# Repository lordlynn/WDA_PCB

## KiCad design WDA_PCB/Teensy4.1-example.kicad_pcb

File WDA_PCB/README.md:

# Description
Basic PCB design to go along with the code developed for Wireless Data Acquisition.

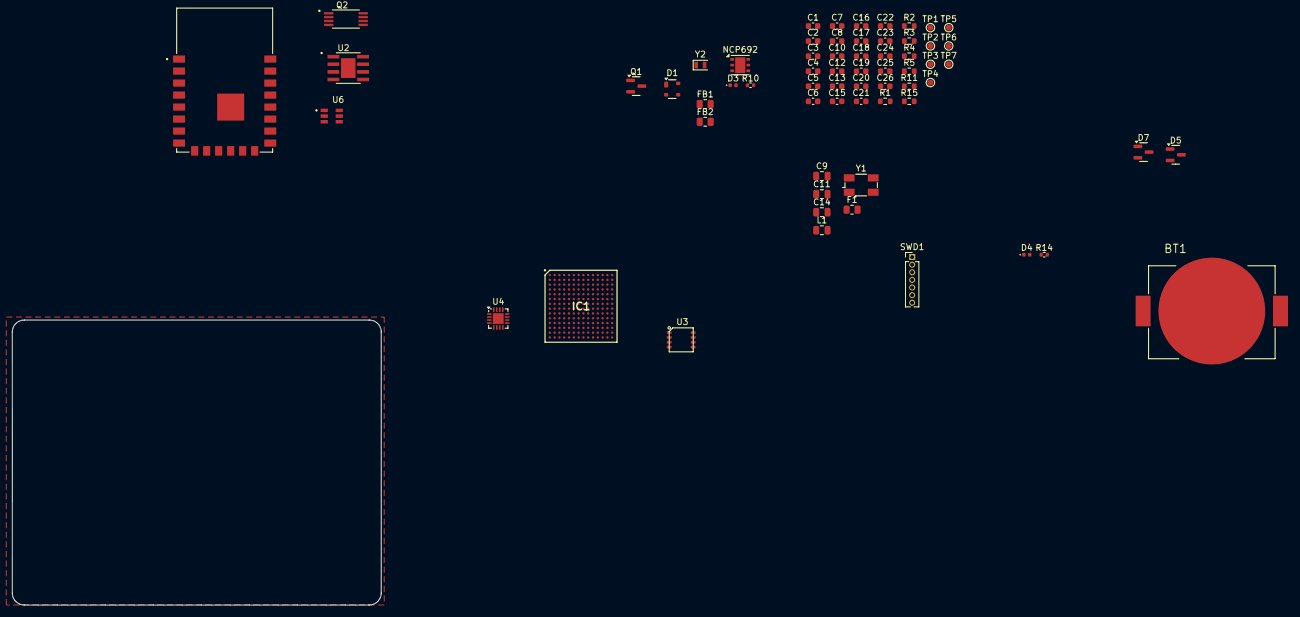
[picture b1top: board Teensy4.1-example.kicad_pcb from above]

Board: 4 copper layers, 61.5 x 47.5 mm, 64 parts (0 on the bottom side), 49 nets, no tracks yet.

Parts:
BT1: BAT-HLD-001; BAT_BAT-HLD-001
C1, C2, C4, C8, C10, C13, C17, C18, C23, C25: 0.22uf; C_0603_1608Metric
C3, C7: 2.2uf; C_0603_1608Metric
C5, C16: 10nf; C_0603_1608Metric
C6, C12, C15, C24, C26: 4.7uf; C_0603_1608Metric
C9, C11, C14: 10uf; C_0805_2012Metric
C19, C20: 10pf; C_0603_1608Metric
C21, C22: 9pf; C_0603_1608Metric
D1: SP0503BAHT; SOT-143
D3, D4: LED; LED_0402_1005Metric
D5, D7: BAT54C; SOT-23
F1: Fuse; R_0805_2012Metric
FB1, FB2: Ferrite_Bead; R_0805_2012Metric
IC1: MIMXRT1062DVJ6B; BGA196C80P14X14_1200X1200X152
L1: 4.7uH; C_0805_2012Metric
NCP692: OnSemi NCP692, fixed version; DFN-6-1EP_3x3mm_P0.95mm_EP1.7x2.6mm
Q1: Q_PMOS_GDS_DMP3125L; SOT-23
Q2: FS8205A; SOP65P640X120-8N
R1, R2: 5.1k; R_0603_1608Metric
R3, R4, R11: 100k; R_0603_1608Metric
R5: 1M; R_0603_1608Metric
R10, R14: 1k; R_0402_1005Metric
R15: 2.2M; R_0603_1608Metric
SWD1: SWD; PinHeader_1x07_P1.27mm_Vertical
TP1, TP2, TP3, TP4, TP5, TP6, TP7: TestPoint; TestPoint_Pad_D1.0mm
U2: TP4056; SOP127P600X175-9N
U3: W25Q64JVXGIM; XSON8_4x4mm
U4: MKL02Z32VFG4; VQFN-16-1EP_3x3mm_P0.5mm_EP1.8x1.8mm
U5: WIZFI360-PA; XCVR_WIZFI360-PA
U6: DW01A; SOT95P280X145-6N
Y1: Crystal_GND23; Crystal_SMD_Abracon_ABM3B-4Pin_5.0x3.2mm
Y2: Crystal; Crystal_SMD_2012-2Pin_2.0x1.2mm

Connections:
+3V3: C4.1, C5.1, C6.1, C7.1, C17.1, D4.2 (A), D5.2, FB2.2, IC1.E6 (NVCC_EMC_1), IC1.E9 (NVCC_GPIO_1), IC1.F5 (NVCC_EMC_2), IC1.F10 (NVCC_GPIO_2), IC1.J6 (NVCC_SD0), IC1.J10 (NVCC_GPIO_3), IC1.K4 (DCDC__IN_Q), IC1.K5 (NVCC_SD1), IC1.N14 (VDDA_ADC_3P3), IC1.P12 (VDD_HIGH_IN), NCP692.4 (OUT), NCP692.5 (SNS), R4.2, TP2.1, U3.8 (VDD), U4.1 (VDD/VREFH), U5.8 (VCC)
+5V: C1.1, C2.1, C3.1, IC1.N6 (USB_OTG1_VBUS), IC1.P6 (USB_OTG2_VBUS), NCP692.1 (IN), NCP692.6 (IN), Q1.3 (S), TP1.1, U2.4 (VCC), U2.8 (CE)
+5VD: D1.2 (K), F1.1
/BAT_GND: Q2.2, Q2.3, U6.6 (GND)
/Bat-: Q2.6, Q2.7
/D0: IC1.G11 (GPIO_AD_B0_03), U5.22 (TXD1)
/D1: IC1.M11 (GPIO_AD_B0_02), U5.21 (RXD1)
/D13: IC1.D8 (GPIO_B0_03), R14.1
/DCDC_PSWITCH: IC1.G10 (GPIO_AD_B0_11), IC1.K3 (DCDC_PSWITCH), R11.2, SWD1.1, U4.3 (PTA3)
/JTAG_MOD: IC1.F13 (GPIO_AD_B0_08), SWD1.5, U4.13 (PTB5/IRQ_12)
/JTAG_TCK: IC1.F12 (GPIO_AD_B0_07), SWD1.2, U4.8 (PTB0/IRQ_5)
/JTAG_TDI: IC1.F14 (GPIO_AD_B0_09), SWD1.4, U4.7 (PTA7/IRQ_4)
/JTAG_TDO: IC1.G13 (GPIO_AD_B0_10), SWD1.3, U4.6 (PTA6)
/JTAG_TMS: IC1.E14 (GPIO_AD_B0_06), SWD1.6, U4.5 (PTA5)
/PMIC_ON_REQ_PWR_SEQ: IC1.K7 (PMIC_ON_REQ), NCP692.3 (EN), R4.1, TP3.1
/POR_B: IC1.M7 (POR_B), U4.9 (PTB1/IRQ_6)
/RTC_BAT: BT1.P1, BT1.P2, D5.1
/SOC_CAP_NET: C13.1, C14.1, C15.1, C16.1, IC1.F6 (VDD_SOC_IN_1), IC1.F7 (VDD_SOC_IN_2), IC1.F8 (VDD_SOC_IN_3), IC1.F9 (VDD_SOC_IN_4), IC1.G6 (VDD_SOC_IN_5), IC1.G9 (VDD_SOC_IN_6), IC1.H6 (VDD_SOC_IN_7), IC1.H9 (VDD_SOC_IN_8), IC1.J5 (DCDC_SENSE), IC1.J9 (VDD_SOC_IN_9), L1.2
/USB1_DN: D1.3 (K), IC1.M8 (USB_OTG1_DN)
/USB1_DP: D1.4 (K), IC1.L8 (USB_OTG1_DP)
GND: BT1.N1, C1.2, C2.2, C3.2, C4.2, C5.2, C6.2, C7.2, C8.2, C9.2, C10.2, C11.2, C12.2, C13.2, C14.2, C15.2, C16.2, C17.2, C18.2, C19.2, C20.2, C21.2, C22.2, C23.2, C24.2, C25.2, C26.2, D1.1 (A), D3.1 (K), IC1.A1 (VSS_1), IC1.A14 (VSS_2), IC1.B5 (VSS_3), IC1.B10 (VSS_4), IC1.E2 (VSS_5), IC1.E13 (VSS_6), IC1.G7 (VSS_7), IC1.G8 (VSS_8), IC1.G14 (GPIO_AD_B0_05), IC1.H7 (VSS_9), IC1.H8 (VSS_10), IC1.J7 (VSS_11), IC1.J8 (VSS_12), IC1.K2 (VSS_13), IC1.K9 (NGND_KEL0), IC1.K13 (VSS_14), IC1.L9 (VSS_15), IC1.N1 (DCDC_GND_1), IC1.N2 (DCDC_GND_2), IC1.N5 (VSS_16), IC1.N8 (VSS_17), IC1.P1 (VSS_18), IC1.P14 (VSS_19), NCP692.2 (GND), NCP692.7 (GND), R1.1, R2.1, R3.1, R5.1, R11.1, R15.1, SWD1.7, U2.1 (TEMP), U2.3 (GND), U3.4 (GND), U4.2 (VSS/VREFL), U4.17 (EPAD), U5.15 (GND), Y1.2, Y1.4
unnamed: D3.2 (A), R14.2
unnamed: D4.1 (K), R10.2
unnamed: F1.2, FB1.1
unnamed: C10.1, C11.1, C12.1, FB2.1, IC1.L1 (DCDC_IN_1), IC1.L2 (DCDC_IN_2)
unnamed: IC1.M1 (DCDC_LP_1), IC1.M2 (DCDC_LP_2), L1.1
unnamed: IC1.F11 (GPIO_AD_B0_04), U4.4 (PTA4)
unnamed: IC1.D10 (GPIO_B0_13), U4.12 (PTB4/IRQ_11)
unnamed: IC1.F3 (GPIO_EMC_01), U4.15 (PTA1/IRQ_1/LPTMR0_ALT1)
unnamed: IC1.L3 (GPIO_SD_B1_06), U3.1 (CS)
unnamed: IC1.L4 (GPIO_SD_B1_07), U3.6 (CLK)
unnamed: IC1.P3 (GPIO_SD_B1_08), U3.5 (D0)
unnamed: IC1.N4 (GPIO_SD_B1_09), U3.2 (D1)
unnamed: IC1.P4 (GPIO_SD_B1_10), U3.3 (D2)
unnamed: IC1.P5 (GPIO_SD_B1_11), U3.7 (D3)
unnamed: C25.1, C26.1, IC1.P10 (NVCC_PLL), TP7.1
unnamed: C21.1, IC1.N9 (RTC_XTALI), Y2.2
unnamed: C22.1, IC1.P9 (RTC_XTALO), Y2.1
unnamed: C23.1, C24.1, IC1.P8 (VDD_HIGH_CAP), TP6.1
unnamed: C18.1, IC1.M10 (VDD_SNVS_CAP), TP5.1
unnamed: D5.3, D7.3, IC1.M9 (VDD_SNVS_IN)
unnamed: C8.1, C9.1, D7.1, IC1.K8 (VDD_USB_CAP), TP4.1
unnamed: C20.1, IC1.P11 (XTALI), R15.2, Y1.1
unnamed: C19.1, IC1.N11 (XTALO), Y1.3
unnamed: FB1.2, Q1.2 (D)
unnamed: Q1.1 (G), R3.2
unnamed: R10.1, U4.11 (PTB3/IRQ_10)
unnamed: Q2.5, U6.3 (OC)
unnamed: Q2.4, U6.1 (OD)

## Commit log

2024-11-25 Initial upload of WDA PCB
